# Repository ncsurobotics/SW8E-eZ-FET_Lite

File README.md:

# URC_eZ-FET_Lite

Standalone ez-FET lite programmer for MSP-430 MCUs. Based on open source design used on TI launchpad development boards, however designed to be more easily assembled and work without a launchpad.

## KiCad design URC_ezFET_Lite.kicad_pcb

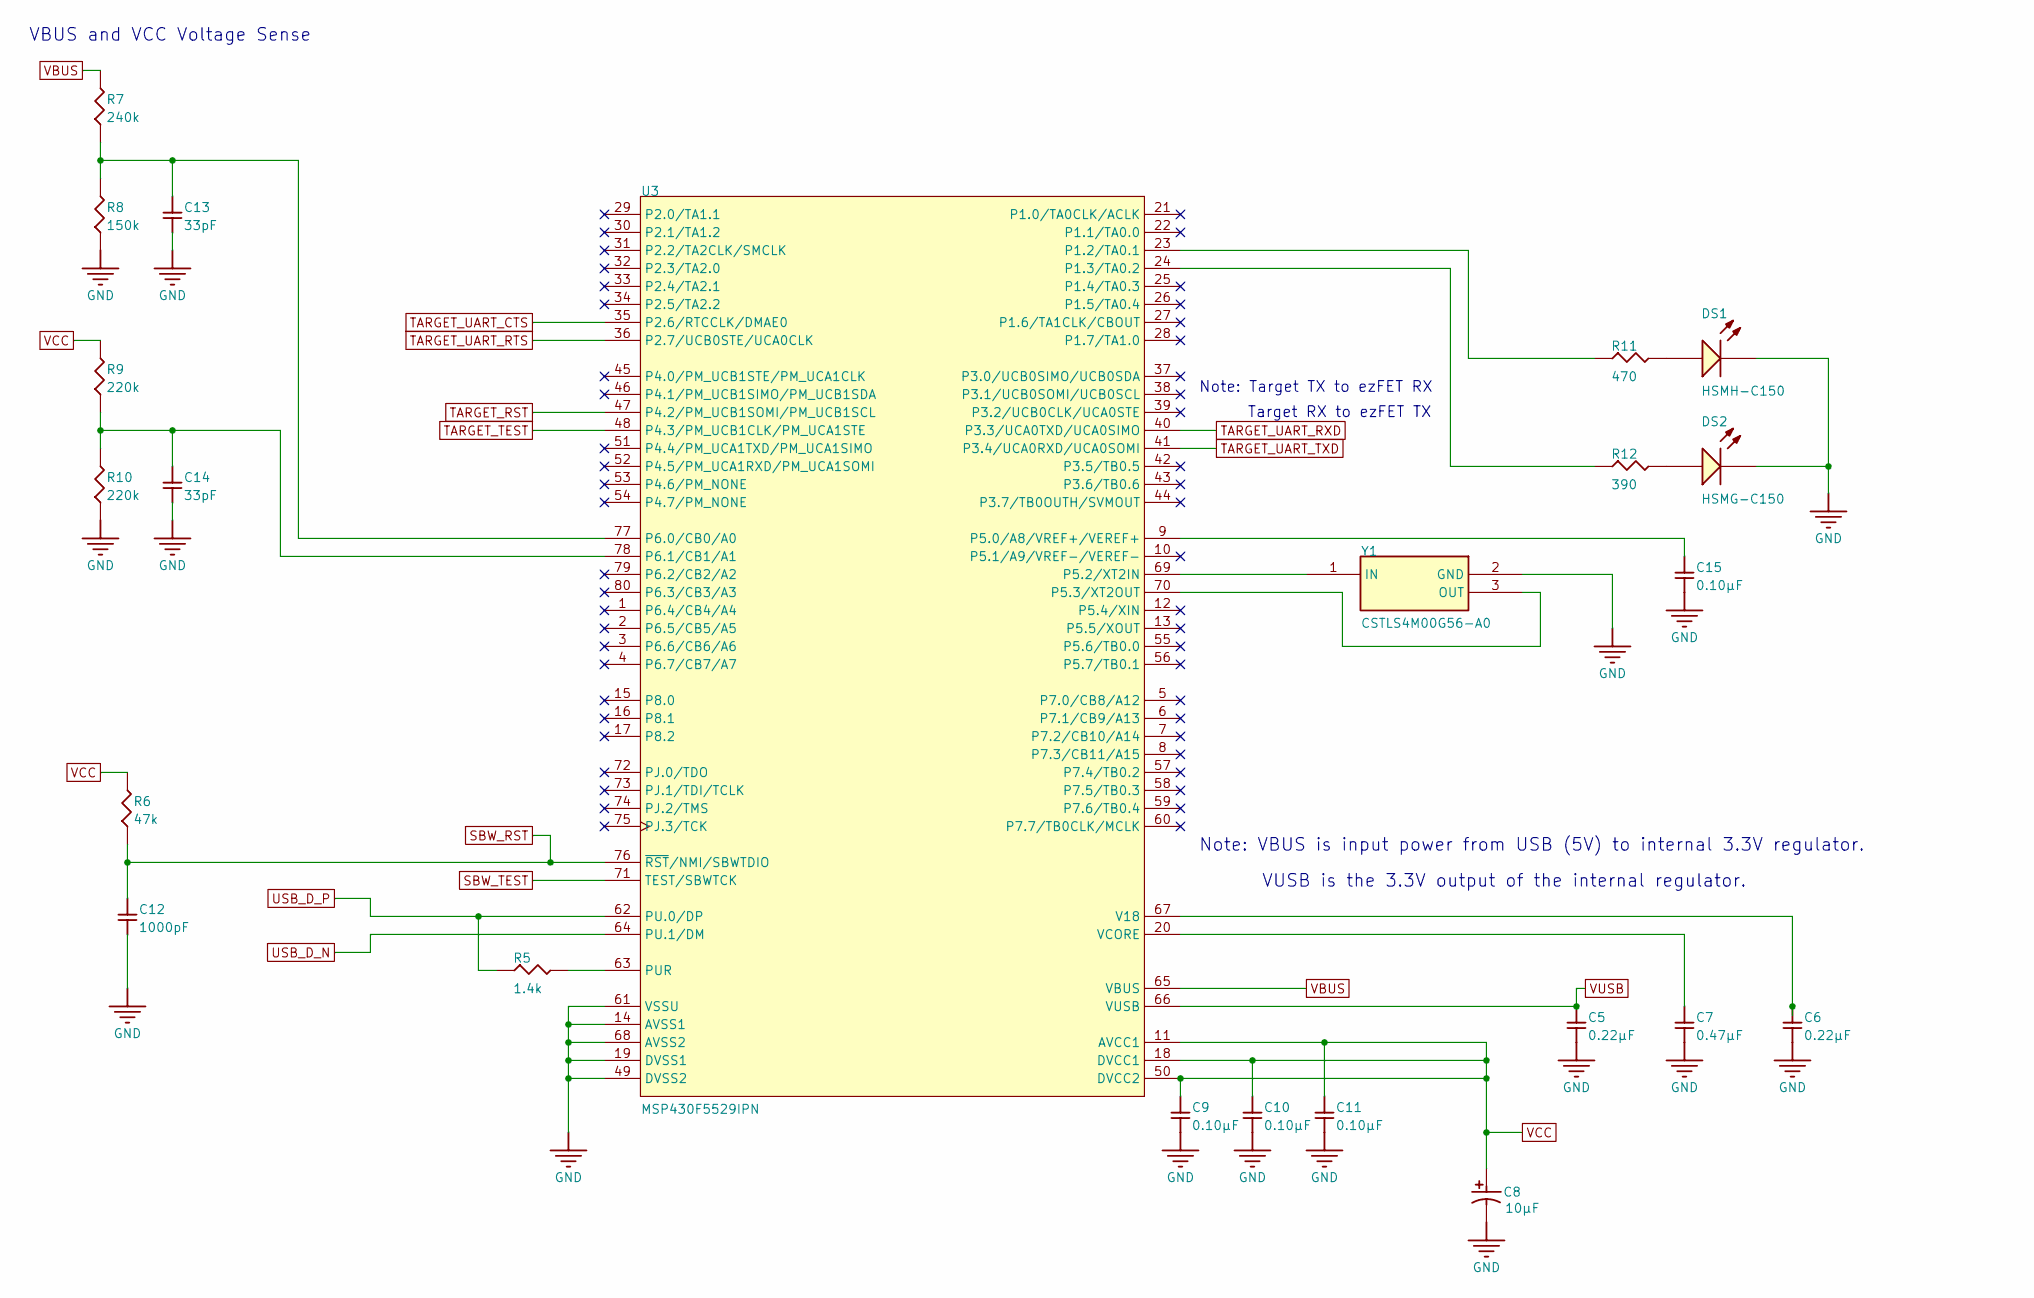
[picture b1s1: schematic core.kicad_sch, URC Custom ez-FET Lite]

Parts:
C5, C6: 0.22µF; SMD-1206C; TOLERANCE ±10%; VOLTAGE 50V; PART NUMBER GCM31MR71H224KA37L; DIGI-KEY PART NUMBER 490-8059-1-ND
C7: 0.47µF; SMD-1206C; TOLERANCE ±10%; VOLTAGE 50V; PART NUMBER GCM31MR71H474KA37L; DIGI-KEY PART NUMBER 490-8061-1-ND
C8: T491A106K010AT; KEMT-A-3216-18-2_M; VOLTAGE - RATED 10V; TOLERANCE ±10%
C9, C10, C11: 0.10µF; SMD-1206C; TOLERANCE ±10%; VOLTAGE 50V; PART NUMBER GCM319R71H104KA37D; DIGI-KEY PART NUMBER 490-11166-1-ND
C12: 1000pF; SMD-1206C; TOLERANCE ±10%; VOLTAGE 50V; PART NUMBER GRM319R71H102KA01D; DIGI-KEY PART NUMBER 490-11610-1-ND
C13, C14: 33pF; SMD-1206C; TOLERANCE ±5%; VOLTAGE 630V; PART NUMBER GCM31A7U2J330JX01D; DIGI-KEY PART NUMBER 490-5040-1-ND
C15: 0.10µF; SMD-1206C; TOLERANCE ±10%; VOLTAGE 250V; PART NUMBER GCJ31CR72E104KXJ3L; DIGI-KEY PART NUMBER 490-12647-1-ND
DS1: HSMH-C150; AVAG-HSMX-C150_V; FORWARD VOLTAGE 2.6V; REVERSE VOLTAGE 5V
DS2: HSMG-C150; AVAG-HSMX-C150_V; FORWARD VOLTAGE VF MAX 2.6V; VOLTAGE VF MIN 2.2V
R5: 1.4k; SMD-0805-RES; TOLERANCE ±1%; PART NUMBER ERJ-6ENF1401V; DIGI-KEY PART NUMBER P1.40KCCT-ND
R6: 47k; SMD-1206-RES; TOLERANCE ±5%; PART NUMBER ERJ-P08J473V; DIGI-KEY PART NUMBER P47KALCT-ND
R7: 240k; SMD-1206-RES; TOLERANCE ±5%; PART NUMBER ERJ-P08J244V; DIGI-KEY PART NUMBER P240KALCT-ND
R8: 150k; SMD-1206-RES; TOLERANCE ±5%; PART NUMBER ERJ-P08J154V; DIGI-KEY PART NUMBER P150KALCT-ND
R9, R10: 220k; SMD-1206-RES; TOLERANCE ±5%; PART NUMBER ERJ-P08J224V; DIGI-KEY PART NUMBER P220KALCT-ND
R11: 470; SMD-1206-RES; TOLERANCE ±1%; PART NUMBER ERJ-8ENF4700V; DIGI-KEY PART NUMBER P470FCT-ND
R12: 390; SMD-1206-RES; TOLERANCE ±1%; PART NUMBER ERJ-8ENF3900V; DIGI-KEY PART NUMBER P390FCT-ND
U3: MSP430F5529IPN; PN0080A_L; PARTNUMBER MSP430F5529IPN
Y1: CSTLS4M00G56-A0; CSTLS_G; MANUFACTURER_PART_NUMBER CSTLS4M00G56-A0

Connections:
GND: C5.2, C6.2, C7.2, C8.2, C9.2, C10.2, C11.2, C12.2, C13.2, C14.2, C15.2, DS1.2 (K), DS2.2 (K), R8.1, R10.1, U3.14 (AVSS1), U3.19 (DVSS1), U3.49 (DVSS2), U3.61 (VSSU), U3.68 (AVSS2), Y1.2 (GND); also elsewhere on the board
unnamed: DS1.1 (A), R11.2
unnamed: DS2.1 (A), R12.2
unnamed: R11.1, U3.23 (P1.2/TA0.1)
unnamed: R12.1, U3.24 (P1.3/TA0.2)
unnamed: C15.1, U3.9 (P5.0/A8/VREF+/VEREF+)
unnamed: U3.69 (P5.2/XT2IN), Y1.1 (IN)
unnamed: U3.70 (P5.3/XT2OUT), Y1.3 (OUT)
unnamed: C13.1, R7.1, R8.2, U3.77 (P6.0/CB0/A0)
unnamed: C14.1, R9.1, R10.2, U3.78 (P6.1/CB1/A1)
unnamed: R5.2, U3.63 (PUR)
unnamed: C6.1, U3.67 (V18)
unnamed: C7.1, U3.20 (VCORE)
SBW_RST: C12.1, R6.1, U3.76 (~RST/NMI/SBWTDIO)
SBW_TEST: U3.71 (TEST/SBWTCK)
TARGET_RST: U3.47 (P4.2/PM_UCB1SOMI/PM_UCB1SCL); also elsewhere on the board
TARGET_TEST: U3.48 (P4.3/PM_UCB1CLK/PM_UCA1STE); also elsewhere on the board
TARGET_UART_CTS: U3.35 (P2.6/RTCCLK/DMAE0); also elsewhere on the board
TARGET_UART_RTS: U3.36 (P2.7/UCB0STE/UCA0CLK); also elsewhere on the board
TARGET_UART_RXD: U3.40 (P3.3/UCA0TXD/UCA0SIMO); also elsewhere on the board
TARGET_UART_TXD: U3.41 (P3.4/UCA0RXD/UCA0SOMI); also elsewhere on the board
USB_D_N: U3.64 (PU.1/DM); also elsewhere on the board
USB_D_P: R5.1, U3.62 (PU.0/DP); also elsewhere on the board
VBUS: R7.2, U3.65 (VBUS); also elsewhere on the board
VCC: C8.1, C9.1, C10.1, C11.1, R6.2, R9.2, U3.11 (AVCC1), U3.18 (DVCC1), U3.50 (DVCC2); also elsewhere on the board
VUSB: C5.1, U3.66 (VUSB)

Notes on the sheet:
Note: VBUS is input power from USB (5V) to internal 3.3V regulator.
VBUS and VCC Voltage Sense
Note: Target TX to ezFET RX
Target RX to ezFET TX
VUSB is the 3.3V output of the internal regulator.

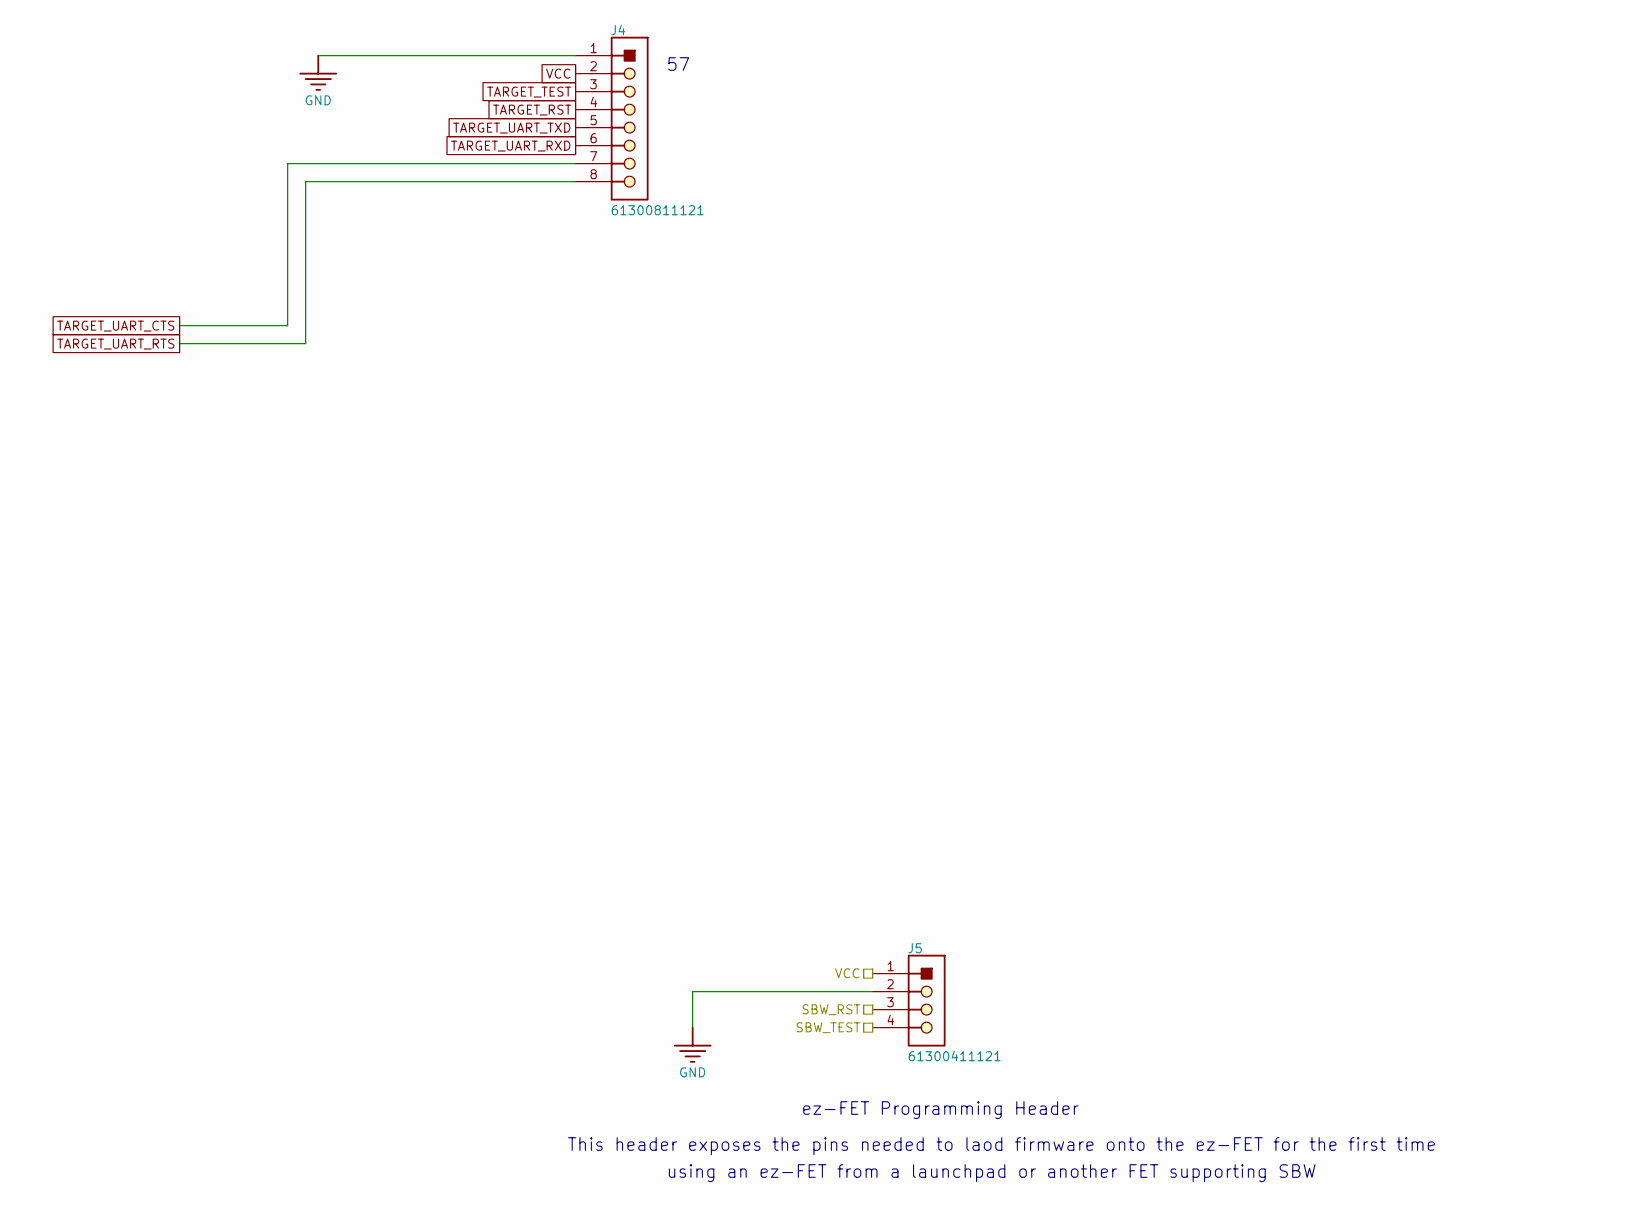
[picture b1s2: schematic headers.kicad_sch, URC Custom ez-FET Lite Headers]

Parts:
J4: 61300811121; WORKING VOLTAGE 250VAC; WITHSTANDING VOLTAGE 500VAC; PART NUMBER 61300811121
J5: 61300411121; WITHSTANDING VOLTAGE 500VAC; WORKING VOLTAGE 250VAC; PART NUMBER 61300411121

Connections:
/headers/SBW_RST: J5.3
/headers/SBW_TEST: J5.4
GND: J4.1, J5.2; also elsewhere on the board
TARGET_RST: J4.4; also elsewhere on the board
TARGET_TEST: J4.3; also elsewhere on the board
TARGET_UART_CTS: J4.7; also elsewhere on the board
TARGET_UART_RTS: J4.8; also elsewhere on the board
TARGET_UART_RXD: J4.6; also elsewhere on the board
TARGET_UART_TXD: J4.5; also elsewhere on the board
VCC: J4.2, J5.1; also elsewhere on the board

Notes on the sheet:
ez-FET Programming Header
using an ez-FET from a launchpad or another FET supporting SBW
This header exposes the pins needed to laod firmware onto the ez-FET for the first time

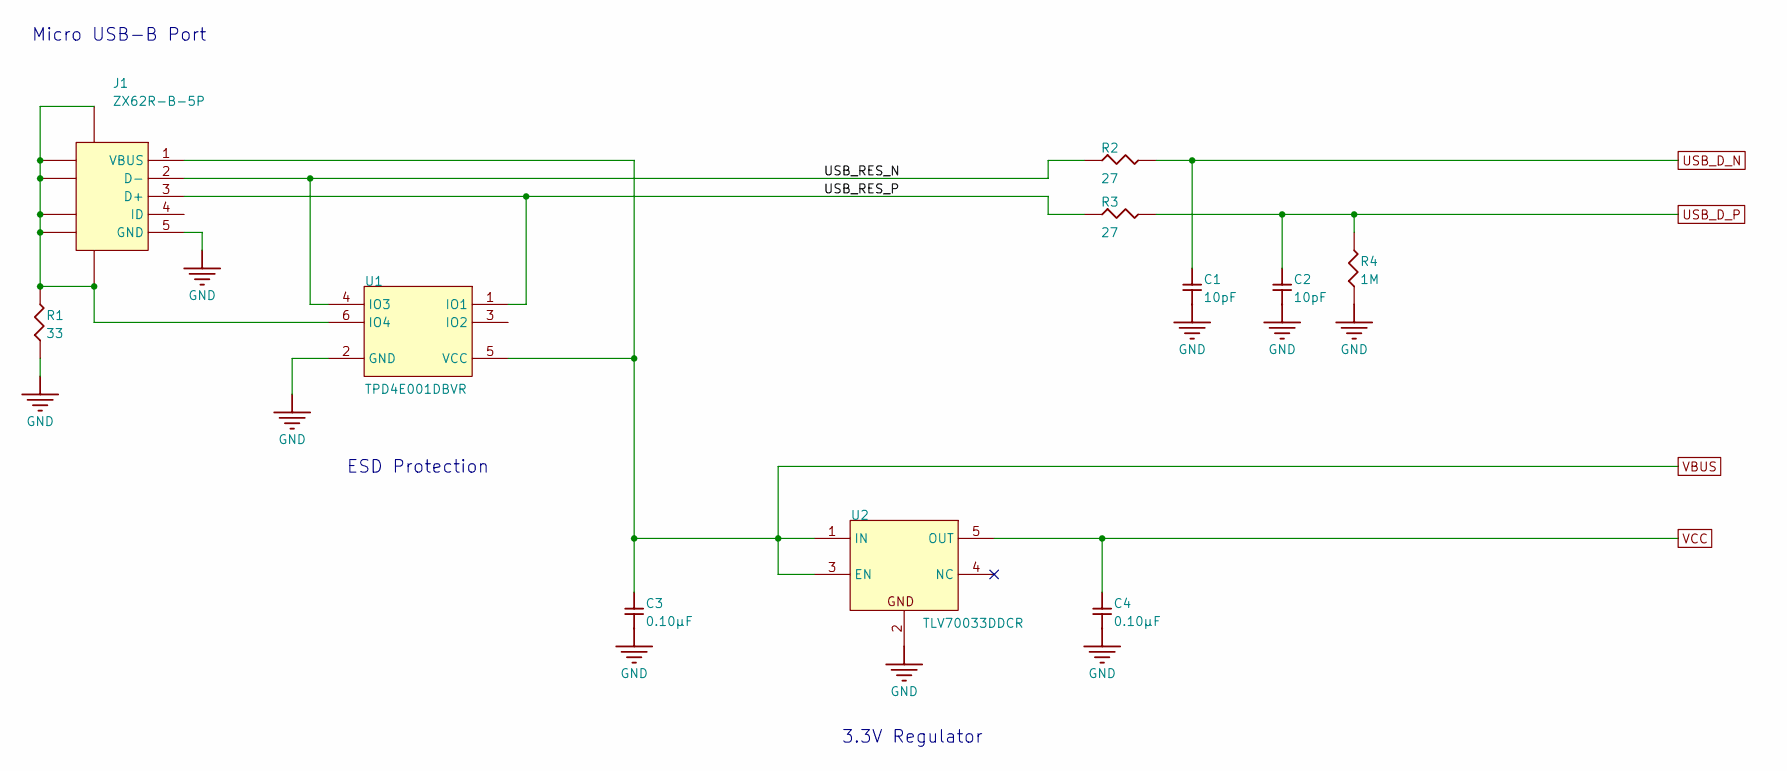
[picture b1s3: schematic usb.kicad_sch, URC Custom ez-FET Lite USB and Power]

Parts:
C1, C2: 10pF; SMD-1206C; TOLERANCE ±5%; VOLTAGE 630V; PART NUMBER GCM31A7U2J100JX01D; DIGI-KEY PART NUMBER 490-5037-1-ND
C3, C4: 0.10µF; SMD-1206C; TOLERANCE ±10%; VOLTAGE 50V; PART NUMBER GCM319R71H104KA37D; DIGI-KEY PART NUMBER 490-11166-1-ND
J1: ZX62R-B-5P; HIRO-ZX62R-B-5P_V; PARTNUMBER ZX62R-B-5P
R1: 33; SMD-0805-RES; TOLERANCE ±1%; PART NUMBER ERJ-6ENF33R0V; DIGI-KEY PART NUMBER P33.0CCT-ND
R2, R3: 27; SMD-0805-RES; TOLERANCE ±5%; PART NUMBER ERJ-P06J270V; DIGI-KEY PART NUMBER P27ADCT-ND
R4: 1M; SMD-0805-RES; TOLERANCE ±5%; PART NUMBER ERJ-P06J105V; DIGI-KEY PART NUMBER P1.0MADCT-ND
U1: TPD4E001DBVR; DBV0006A_M; BREAKDOWN VOLTAGE(MIN)(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 11; PARTNUMBER TPD4E001DBVR
U2: TLV70033DDCR; DDC0005A_M; PARTNUMBER TLV70033DDCR

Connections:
/usb/USB_RES_N: J1.2 (D-), R2.1, U1.4 (IO3)
/usb/USB_RES_P: J1.3 (D+), R3.1, U1.1 (IO1)
GND: C1.2, C2.2, C3.2, C4.2, J1.5 (GND), R1.1, R4.1, U1.2 (GND), U2.2 (GND); also elsewhere on the board
unnamed: J1.6 (SHLD), J1.7 (SHLD), J1.8 (SHLD), J1.9 (SHLD), J1.10 (SHLD), J1.11 (SHLD), R1.2, U1.6 (IO4)
USB_D_N: C1.1, R2.2; also elsewhere on the board
USB_D_P: C2.1, R3.2, R4.2; also elsewhere on the board
VBUS: C3.1, J1.1 (VBUS), U1.5 (VCC), U2.1 (IN), U2.3 (EN); also elsewhere on the board
VCC: C4.1, U2.5 (OUT); also elsewhere on the board

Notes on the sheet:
Micro USB-B Port
3.3V Regulator
ESD Protection

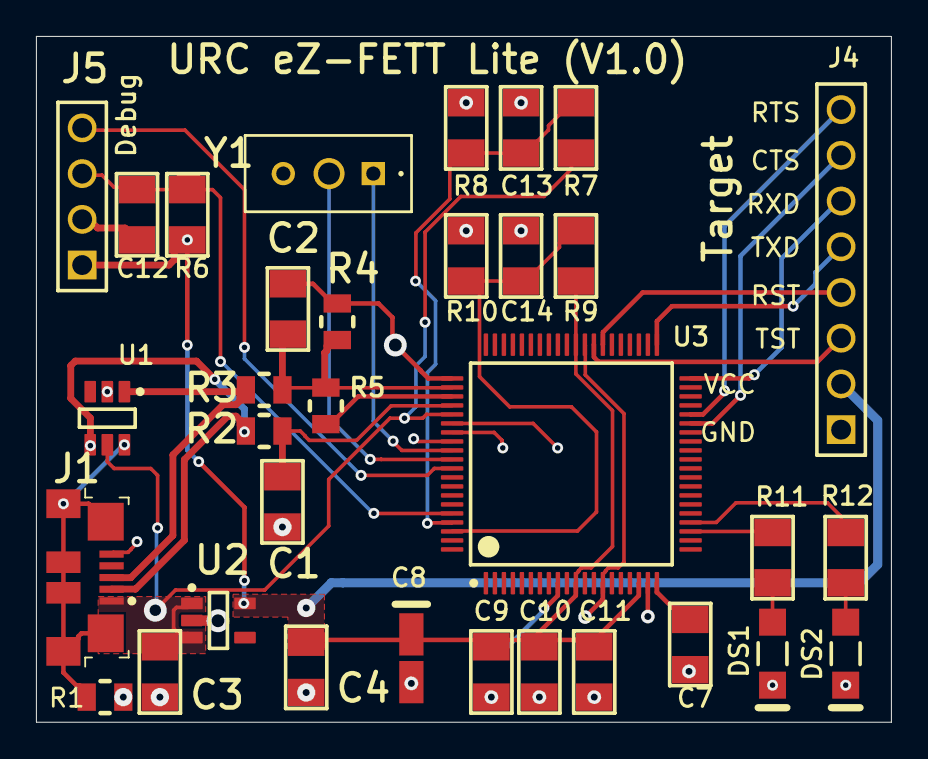
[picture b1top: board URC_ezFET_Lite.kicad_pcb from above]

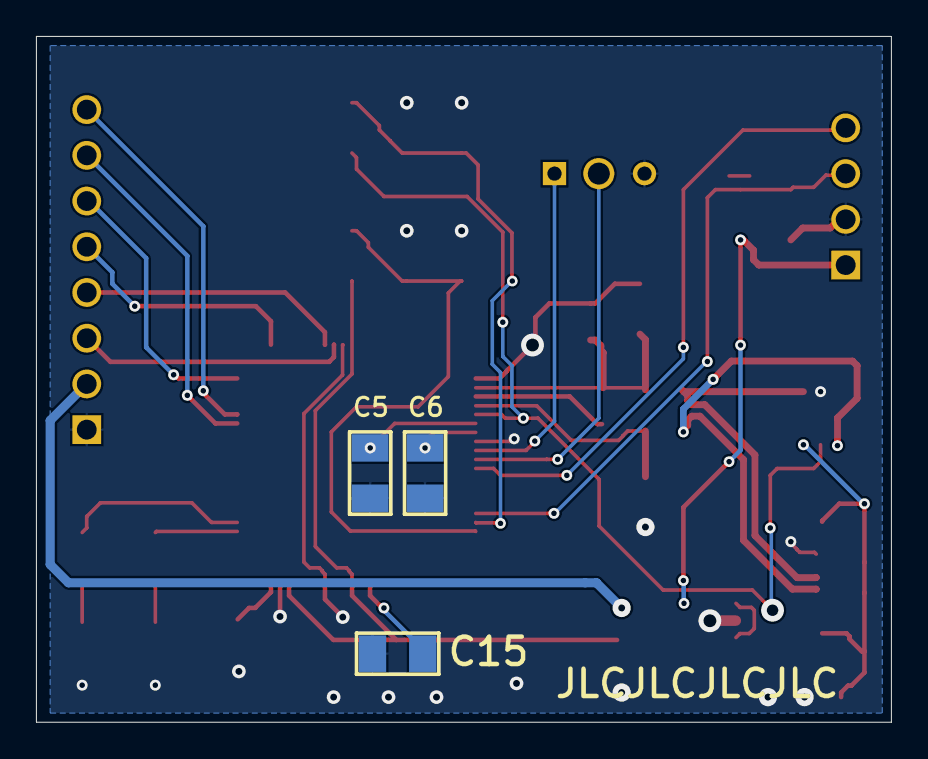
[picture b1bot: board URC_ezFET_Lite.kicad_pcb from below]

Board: 2 copper layers, 47.5 x 38.1 mm, 36 parts (3 on the bottom side), 28 nets.

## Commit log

2020-02-16 Added schematic using correct MSP430 chip
2020-03-29 Cleaning up schematic
2020-03-29 Finished headers schematic
2020-03-30 Fixed some errors and updated title blocks
2020-03-30 Added CTS and RTS
2020-04-01 Added SBW interface header to program ez FET for first time
2020-04-09 Fix some errors and change chip
2020-07-12 First attempt at USB routing
2020-07-18 Added 0805 resistor lib and changed out USB related resistors
2020-09-09 Bad changes
2020-09-09 Revert "Bad changes"
    This reverts commit d5d6da6243201e2c32460957dcc4f3cf9126dcff.
2022-04-17 Begin work on pcb design
2022-04-17 All but interface header routed
2022-04-17 Finished ez-FET routing
2022-04-17 Add more silkscreen
2022-04-17 Changed traces to cut ground plane less
2022-04-17 Fix silkscreen
2022-06-15 Fixed PCB design rule violations
2022-06-15 Actually commited project this time
2022-06-25 removed thermal reliefs and rerouted some paths
2022-06-28 Add bom
2022-06-30 Different part substitution on bom
2022-06-30 Update ordering bom
2022-06-30 Added board outline
2023-03-22 Imported project to kicad
2023-03-23 Make project name match repo name

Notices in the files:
parts and their libraries:
COPYRIGHT: Copyright (C) 2018 Accelerated Designs. All rights reserved
